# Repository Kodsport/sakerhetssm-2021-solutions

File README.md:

# sakerhetssm-2021
Uppgifter till Säkerhets-SM 2021

I det här repot hittar du källkoden till alla uppgifter från Säkerhets-SM 2021, inklusive dommarlösningar och vissa writeups.

Alla nerladdningsbara uppgiftsfiler ligger i respektive uppgiftsmappar. Uppgifter som hade services har också en `docker-compose.yml` fil som låter er starta uppgifterna lokalt. För att göra det, installera [Docker](https://docs.docker.com/get-docker/) samt [docker-compose](https://docs.docker.com/compose/install/) och kör `docker-compose up` i uppgiftsmappen. Anslut sedan till `127.0.0.1:50000`.

## Lösningsstream

Calle Svensson har streamat när han löser uppgifter från kvalet:

- Del 1 - https://www.youtube.com/watch?v=TzcGTrwnIvc
- Del 2 - https://www.youtube.com/watch?v=_Ki1XHeZ_JM

Några uppgifter gicks även igenom på kvalets avslutningsstream: https://www.youtube.com/watch?v=g92X6ZYR6BI

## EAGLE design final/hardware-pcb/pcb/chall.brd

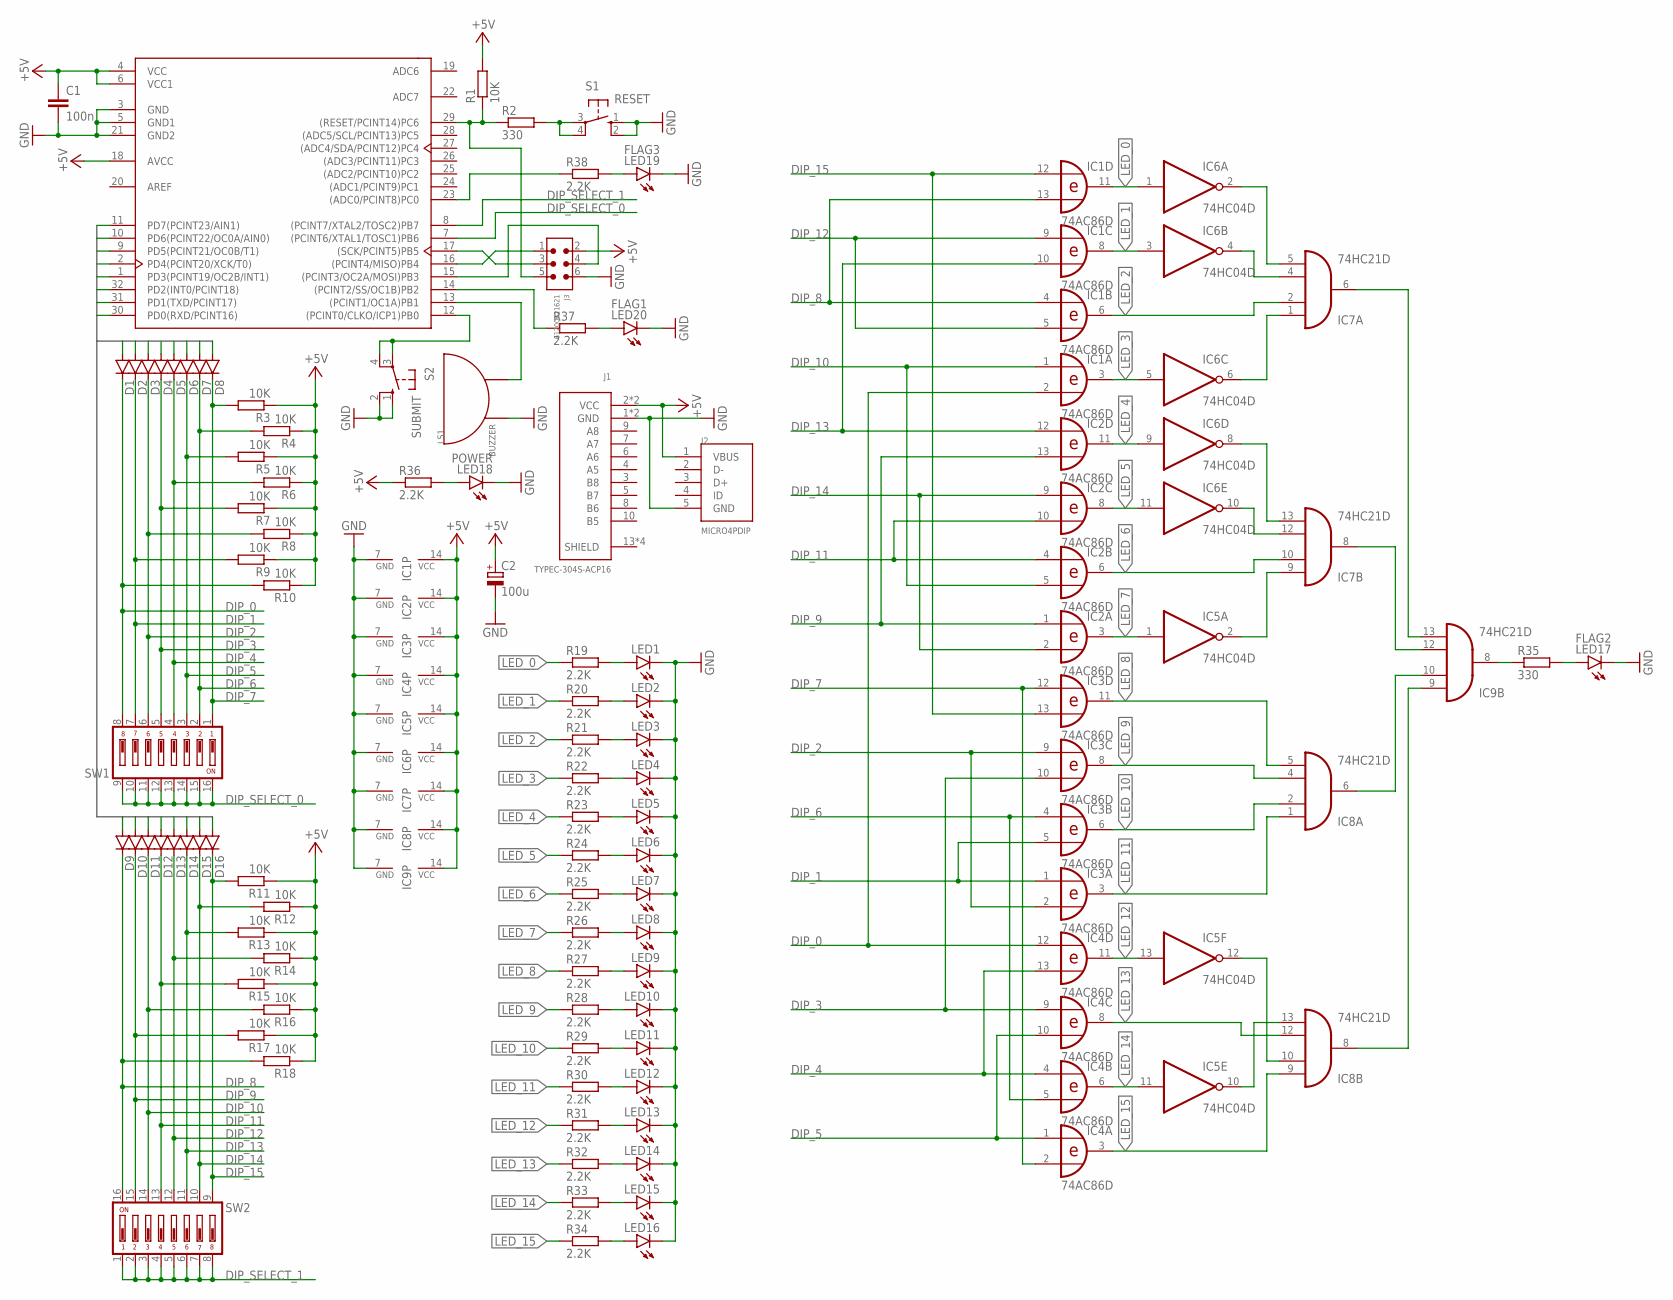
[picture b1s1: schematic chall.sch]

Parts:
C1: 100n; C0805
C2: 100u; E2-5
D1, D2, D3, D4, D5, D6, D7, D8, D9, D10, D11, D12, D13, D14, D15, D16: DIODE-DO-214AC; DO-214AC
IC1, IC2, IC3, IC4: 74AC86D; SO14
IC5, IC6: 74HC04D; SO14
IC7, IC8, IC9: 74HC21D; SO14
J1: TYPEC-304S-ACP16
J2: MICRO4PDIP
J3: 61200621621
LED1, LED2, LED3, LED4, LED5, LED6, LED7, LED8, LED9, LED10, LED11, LED12, LED13, LED14, LED15, LED16: LEDCHIPLED_0603; CHIPLED_0603
LED17: FLAG2; CHIPLED_0603
LED18: POWER; CHIPLED_0603
LED19: FLAG3; CHIPLED_0603
LED20: FLAG1; CHIPLED_0603
LS1: BUZZER
R1, R3, R4, R5, R6, R7, R8, R9, R10, R11, R12, R13, R14, R15, R16, R17, R18: 10K; R0805
R2, R35: 330; R0805
R19, R20, R21, R22, R23, R24, R25, R26, R27, R28, R29, R30, R31, R32, R33, R34, R36, R37, R38: 2.2K; R0805
S1: RESET; B3F-10XX
S2: SUBMIT; B3F-10XX
SW1, SW2: DS08; DS-08
U1: ATMEGA328P-AU; TQFP-32

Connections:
0: D1.A, D16.A, U1.30 (PD0(RXD/PCINT16))
1: D2.A, D15.A, U1.31 (PD1(TXD/PCINT17))
2: D3.A, D14.A, U1.32 (PD2(INT0/PCINT18))
3: D4.A, D13.A, U1.1 (PD3(PCINT19/OC2B/INT1))
4: D5.A, D12.A, U1.2 (PD4(PCINT20/XCK/T0))
5: D6.A, D11.A, U1.9 (PD5(PCINT21/OC0B/T1))
6: D7.A, D10.A, U1.10 (PD6(PCINT22/OC0A/AIN0))
7: D8.A, D9.A, U1.11 (PD7(PCINT23/AIN1))
+5V: C1.1, C2.+, IC1.14 (VCC), IC2.14 (VCC), IC3.14 (VCC), IC4.14 (VCC), IC5.14 (VCC), IC6.14 (VCC), IC7.14 (VCC), IC8.14 (VCC), IC9.14 (VCC), J1.2 (VCC), J1.11 (VCC), J2.1 (VBUS), J3.2, R1.2, R3.1, R4.1, R5.1, R6.1, R7.1, R8.1, R9.1, R10.1, R11.1, R12.1, R13.1, R14.1, R15.1, R16.1, R17.1, R18.1, R36.1, U1.4 (VCC), U1.6 (VCC1), U1.18 (AVCC)
AREF: U1.20 (AREF)
DIP_0: D1.C, IC1.2 (I1), IC4.12 (I0), R10.2, SW1.8
DIP_1: D2.C, IC3.1 (I0), IC3.5 (I1), R9.2, SW1.7
DIP_2: D3.C, IC3.2 (I1), IC3.9 (I0), R8.2, SW1.6
DIP_3: D4.C, IC3.10 (I1), IC4.9 (I0), R7.2, SW1.5
DIP_4: D5.C, IC4.4 (I0), IC4.13 (I1), R6.2, SW1.4
DIP_5: D6.C, IC4.1 (I0), IC4.10 (I1), R5.2, SW1.3
DIP_6: D7.C, IC3.4 (I0), IC4.5 (I1), R4.2, SW1.2
DIP_7: D8.C, IC3.12 (I0), IC4.2 (I1), R3.2, SW1.1
DIP_8: D9.C, IC1.4 (I0), IC1.13 (I1), R18.2, SW2.16
DIP_9: D10.C, IC2.1 (I0), IC2.13 (I1), R17.2, SW2.15
DIP_10: D11.C, IC1.1 (I0), IC2.5 (I1), R16.2, SW2.14
DIP_11: D12.C, IC2.4 (I0), IC2.10 (I1), R15.2, SW2.13
DIP_12: D13.C, IC1.5 (I1), IC1.9 (I0), R14.2, SW2.12
DIP_13: D14.C, IC1.10 (I1), IC2.12 (I0), R13.2, SW2.11
DIP_14: D15.C, IC2.2 (I1), IC2.9 (I0), R12.2, SW2.10
DIP_15: D16.C, IC1.12 (I0), IC3.13 (I1), R11.2, SW2.9
DIP_SELECT_0: SW1.9, SW1.10, SW1.11, SW1.12, SW1.13, SW1.14, SW1.15, SW1.16, U1.7 ((PCINT6/XTAL1/TOSC1)PB6)
DIP_SELECT_1: SW2.1, SW2.2, SW2.3, SW2.4, SW2.5, SW2.6, SW2.7, SW2.8, U1.8 ((PCINT7/XTAL2/TOSC2)PB7)
GND: C1.2, C2.-, IC1.7 (GND), IC2.7 (GND), IC3.7 (GND), IC4.7 (GND), IC5.7 (GND), IC6.7 (GND), IC7.7 (GND), IC8.7 (GND), IC9.7 (GND), J1.1 (GND), J1.12 (GND), J2.5 (GND), J3.6, LED1.C, LED2.C, LED3.C, LED4.C, LED5.C, LED6.C, LED7.C, LED8.C, LED9.C, LED10.C, LED11.C, LED12.C, LED13.C, LED14.C, LED15.C, LED16.C, LED17.C, LED18.C, LED19.C, LED20.C, LS1.1, S1.1 (S), S1.2 (S1), S2.1 (S), S2.2 (S1), U1.3 (GND), U1.5 (GND1), U1.21 (GND2)
LED_0: IC1.11 (O), IC6.1 (I), R19.1
LED_1: IC1.8 (O), IC6.3 (I), R20.1
LED_2: IC1.6 (O), IC7.2 (I1), R21.1
LED_3: IC1.3 (O), IC6.5 (I), R22.1
LED_4: IC2.11 (O), IC6.9 (I), R23.1
LED_5: IC2.8 (O), IC6.11 (I), R24.1
LED_6: IC2.6 (O), IC7.10 (I1), R25.1
LED_7: IC2.3 (O), IC5.1 (I), R26.1
LED_8: IC3.11 (O), IC8.5 (I3), R27.1
LED_9: IC3.8 (O), IC8.4 (I2), R28.1
LED_10: IC3.6 (O), IC8.2 (I1), R29.1
LED_11: IC3.3 (O), IC8.1 (I0), R30.1
LED_12: IC4.11 (O), IC5.13 (I), R31.1
LED_13: IC4.8 (O), IC8.12 (I2), R32.1
LED_14: IC4.6 (O), IC5.11 (I), R33.1
LED_15: IC4.3 (O), IC8.9 (I0), R34.1
unnamed: R2.2, S1.3, S1.4 (P1)
unnamed: LED2.A, R20.2
unnamed: J3.5, R1.1, R2.1, U1.29 ((RESET/PCINT14)PC6)
unnamed: J3.3, U1.17 ((SCK/PCINT5)PB5)
unnamed: IC6.2 (O), IC7.5 (I3)
unnamed: IC6.4 (O), IC7.4 (I2)
unnamed: LED3.A, R21.2
unnamed: IC6.6 (O), IC7.1 (I0)
unnamed: IC6.8 (O), IC7.13 (I3)
unnamed: IC6.10 (O), IC7.12 (I2)
unnamed: LED4.A, R22.2
unnamed: IC5.2 (O), IC7.9 (I0)
unnamed: LED5.A, R23.2
unnamed: LED6.A, R24.2
unnamed: LED7.A, R25.2
unnamed: LED8.A, R26.2
unnamed: IC5.12 (O), IC8.10 (I1)
unnamed: LED9.A, R27.2
unnamed: IC5.10 (O), IC8.13 (I3)
unnamed: LED10.A, R28.2
unnamed: IC7.8 (O), IC9.12 (I2)
unnamed: IC7.6 (O), IC9.13 (I3)
unnamed: IC8.6 (O), IC9.10 (I1)
unnamed: IC8.8 (O), IC9.9 (I0)
unnamed: LED11.A, R29.2
unnamed: LED12.A, R30.2
unnamed: LED13.A, R31.2
unnamed: LED14.A, R32.2
unnamed: LED15.A, R33.2
unnamed: LED16.A, R34.2
unnamed: S2.3, S2.4 (P1), U1.12 ((PCINT0/CLKO/ICP1)PB0)
unnamed: LED19.A, R38.2
unnamed: LED1.A, R19.2
unnamed: R38.1, U1.23 ((ADC0/PCINT8)PC0)
unnamed: LED20.A, R37.2
unnamed: LED17.A, R35.2
unnamed: IC9.8 (O), R35.1
unnamed: LS1.2, U1.13 ((PCINT1/OC1A)PB1)
unnamed: LED18.A, R36.2
unnamed: J3.1, U1.16 ((PCINT4/MISO)PB4)
unnamed: J3.4, U1.15 ((PCINT3/OC2A/MOSI)PB3)
unnamed: R37.1, U1.14 ((PCINT2/SS/OC1B)PB2)

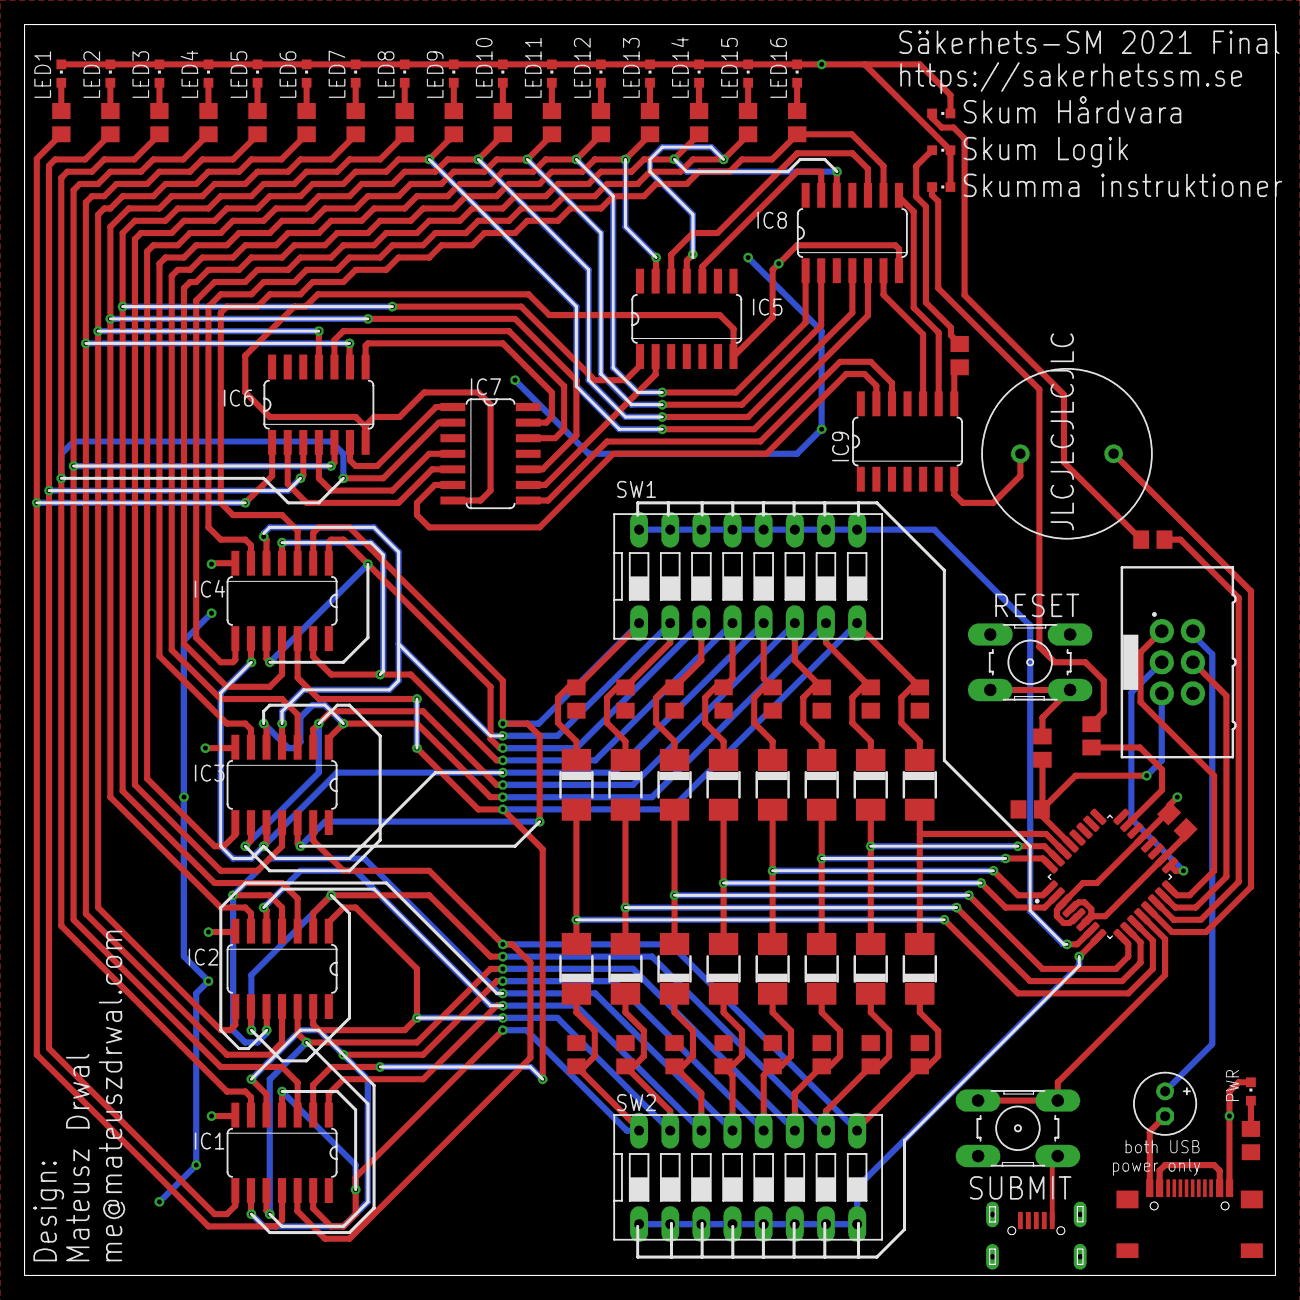
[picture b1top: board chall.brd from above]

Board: 2 copper layers, 102.0 x 102.0 mm, 94 parts (0 on the bottom side), 86 nets.

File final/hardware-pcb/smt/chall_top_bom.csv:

"Comment","Designator","Footprint","LCSC Part #"
"diode","D1 D2 D3 D4 D5 D6 D7 D8 D9 D10 D11 D12 D13 D14 D15 D16","SMA","C95872"
"LED","LED1 LED2 LED3 LED4 LED5 LED6 LED7 LED8 LED9 LED10 LED11 LED12 LED13 LED14 LED15 LED16 LED17 LED18 LED19 LED20","0603","C72041"
"10K","R1 R3 R4 R5 R6 R7 R8 R9 R10 R11 R12 R13 R14 R15 R16 R17 R18","R0805","C17414"
"2.2K","R19 R20 R21 R22 R23 R24 R25 R26 R27 R28 R29 R30 R31 R32 R33 R34 R35 R36 R37 R38","R0805","C17520"
"74AC86D","IC1 IC2 IC3 IC4","SO14","C152540"
"74HC04D","IC5 IC6","SO14","C5590"
"74HC21D","IC7 IC8 IC9","SO14","C5617"
"100n","C1","C0805","C49678"
"330","R2","R0805","C17630"
"ATMEGA328P-AU","U1","TQFP-32","C14877"
"TYPEC-304S-ACP16","J1","TYPEC-304S-ACP16","C720630"
"MICRO4PDIP","J2","MICRO4PDIP","C456008"

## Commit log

2021-04-02 source
2021-05-28 minor fix
2021-06-03 final
2021-06-07 Added links to streams

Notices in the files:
parts and their libraries:
Wurth_Connectors_WR-BHD: Copyright: Würth Elektronik
